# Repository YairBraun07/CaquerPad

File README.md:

# CaquerPad
4x3 macro pad with rotary encoder. Built for HackClub Blueprint Hackpad project. 

---

## 📸 Project Overview 
Here is a look at the finished and functional device.

---

## ⚡ Electronics Design

### Schematic
This is the wiring diagram showing how all components are connected.

### PCB (Printed Circuit Board)
This is the board layout design where the components are soldered.

---

## 📦Case assembly
Views of the 3D printed case and how all the parts fit together.

---

## 🛠 Bill of Materials (BOM)
List of components required to build this project.

| Component | Quantity | Details / Notes |
| :--- | :---: | :--- |
| Microcontroller | 1 | Seeed Studio XIAO RP2040 |
| Switches | 12 | e.g., Cherry MX or Gateron |
| Keycaps | 12 | *Make sure they are compatible* |
| Diodes | 12 | 1N4148 |
| Encoder | 1 | EC11 Rotary Encoder |
| LEDs | 12 | SK6812 Mini-E / WS2812B |
| Case | 1 | 3D Printed (PLA/PETG) |
| Screws | 3 | M3 x 5mm |

---

### Author
* **[Yair Braun]**

### Ethical Considerations: Google Gemini AI was utilized as a general guide throughout the entire project development, assisting with best practices, troubleshooting, and documentation structure."

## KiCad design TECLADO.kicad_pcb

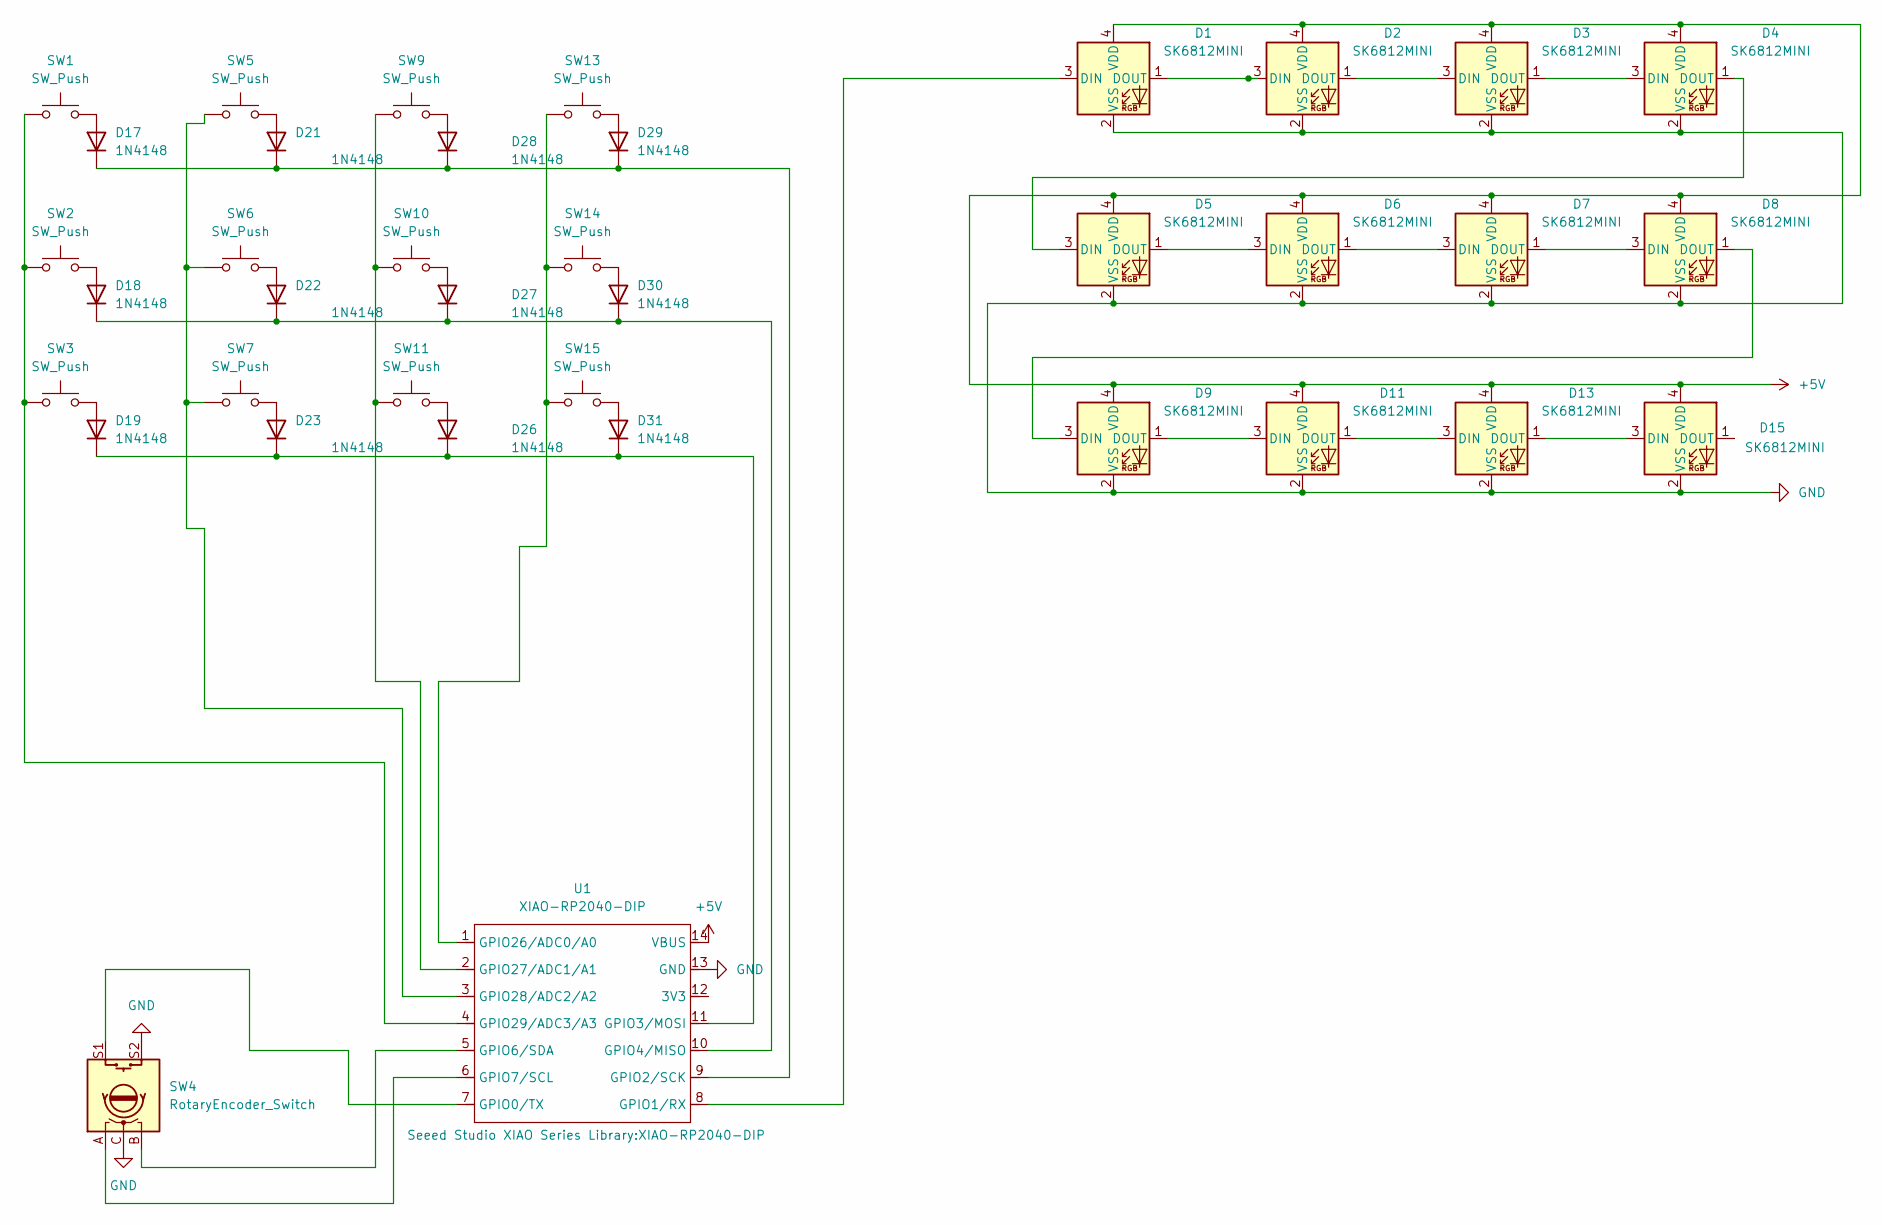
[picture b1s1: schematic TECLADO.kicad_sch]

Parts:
D1, D2, D3, D4, D5, D6, D7, D8, D9, D11, D13, D15: SK6812MINI; LED_SK6812MINI_PLCC4_3.5x3.5mm_P1.75mm
D17, D18, D19, D21, D22, D23, D26, D27, D28, D29, D30, D31: 1N4148; D_DO-35_SOD27_P7.62mm_Horizontal
SW1, SW2, SW3, SW5, SW6, SW7, SW9, SW10, SW11, SW13, SW14, SW15: SW_Push; SW_Cherry_MX_1.00u_PCB
SW4: RotaryEncoder_Switch; RotaryEncoder_Alps_EC11E-Switch_Vertical_H20mm_CircularMoun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
U1: XIAO-RP2040-DIP

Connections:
+5V: D1.4 (VDD), D2.4 (VDD), D3.4 (VDD), D4.4 (VDD), D5.4 (VDD), D6.4 (VDD), D7.4 (VDD), D8.4 (VDD), D9.4 (VDD), D11.4 (VDD), D13.4 (VDD), D15.4 (VDD), U1.14 (VBUS)
GND: D1.2 (VSS), D2.2 (VSS), D3.2 (VSS), D4.2 (VSS), D5.2 (VSS), D6.2 (VSS), D7.2 (VSS), D8.2 (VSS), D9.2 (VSS), D11.2 (VSS), D13.2 (VSS), D15.2 (VSS), SW4.C, SW4.S2, U1.13 (GND)
unnamed: D1.3 (DIN), U1.8 (GPIO1/RX)
unnamed: D1.1 (DOUT), D2.3 (DIN)
unnamed: D2.1 (DOUT), D3.3 (DIN)
unnamed: D3.1 (DOUT), D4.3 (DIN)
unnamed: D4.1 (DOUT), D5.3 (DIN)
unnamed: D5.1 (DOUT), D6.3 (DIN)
unnamed: D6.1 (DOUT), D7.3 (DIN)
unnamed: D7.1 (DOUT), D8.3 (DIN)
unnamed: D8.1 (DOUT), D9.3 (DIN)
unnamed: D9.1 (DOUT), D11.3 (DIN)
unnamed: D11.1 (DOUT), D13.3 (DIN)
unnamed: D13.1 (DOUT), D15.3 (DIN)
unnamed: D17.2 (A), SW1.2
unnamed: D17.1 (K), D21.1 (K), D28.1 (K), D29.1 (K), U1.9 (GPIO2/SCK)
unnamed: D18.2 (A), SW2.2
unnamed: D18.1 (K), D22.1 (K), D27.1 (K), D30.1 (K), U1.10 (GPIO4/MISO)
unnamed: D19.2 (A), SW3.2
unnamed: D19.1 (K), D23.1 (K), D26.1 (K), D31.1 (K), U1.11 (GPIO3/MOSI)
unnamed: D21.2 (A), SW5.2
unnamed: D22.2 (A), SW6.2
unnamed: D23.2 (A), SW7.2
unnamed: D26.2 (A), SW11.2
unnamed: D27.2 (A), SW10.2
unnamed: D28.2 (A), SW9.2
unnamed: D29.2 (A), SW13.2
unnamed: D30.2 (A), SW14.2
unnamed: D31.2 (A), SW15.2
unnamed: SW4.S1, U1.7 (GPIO0/TX)
unnamed: SW4.B, U1.5 (GPIO6/SDA)
unnamed: SW4.A, U1.6 (GPIO7/SCL)
unnamed: SW13.1, SW14.1, SW15.1, U1.1 (GPIO26/ADC0/A0)
unnamed: SW9.1, SW10.1, SW11.1, U1.2 (GPIO27/ADC1/A1)
unnamed: SW5.1, SW6.1, SW7.1, U1.3 (GPIO28/ADC2/A2)
unnamed: SW1.1, SW2.1, SW3.1, U1.4 (GPIO29/ADC3/A3)

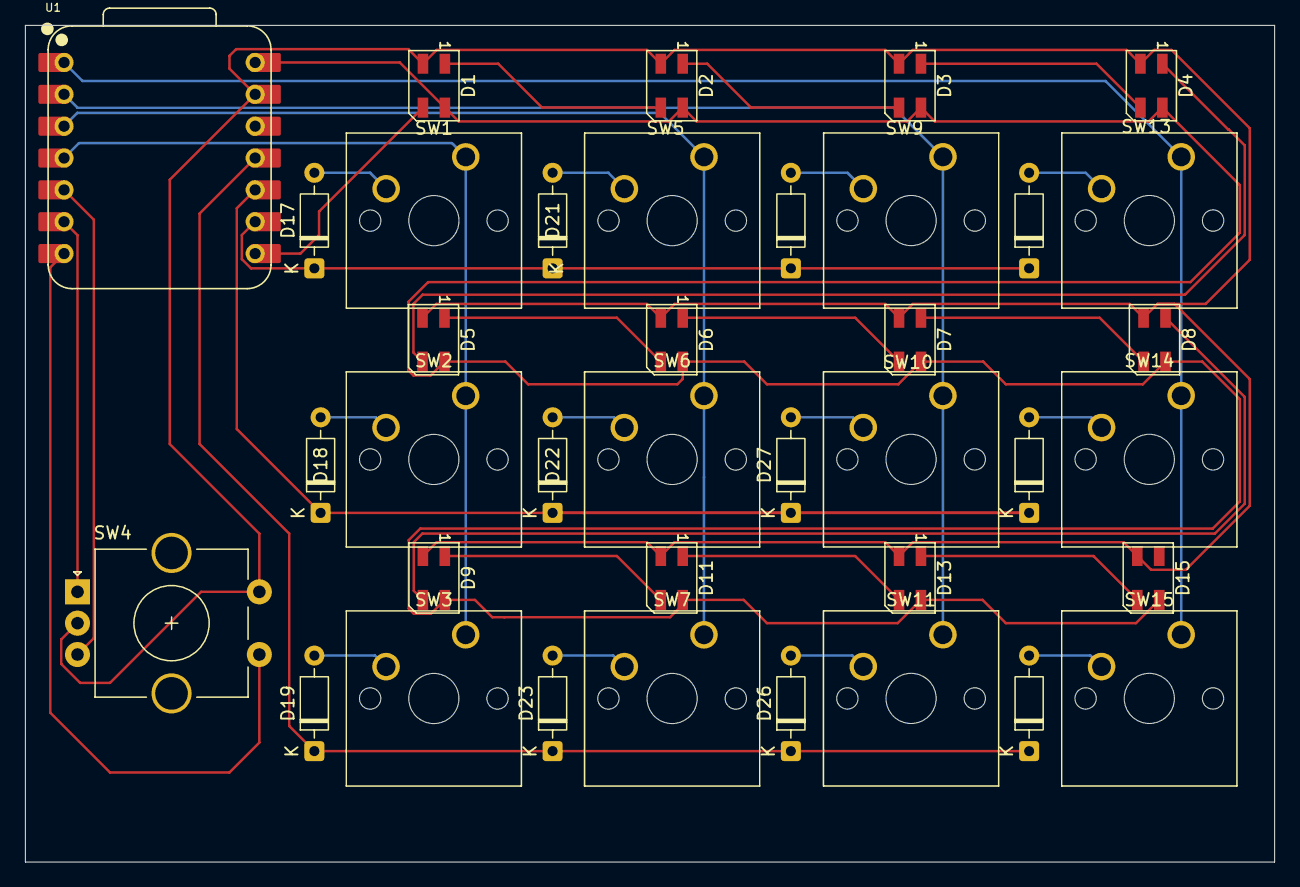
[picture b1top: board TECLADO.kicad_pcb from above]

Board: 2 copper layers, 99.6 x 66.7 mm, 38 parts (0 on the bottom side), 36 nets.

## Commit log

2025-12-14 Add files via upload
    Project file
2025-12-14 KiCad Project file
2025-12-14 Schematics File
2025-12-14 PCB Board File
2025-12-16 Case 3D Model
2025-12-16 Rename CASE_CAQUERPAD.3mf to 3D FILES/CASE_CAQUERPAD.3mf
2025-12-16 FOLDER FOR 3D MODELS
2025-12-16 CODE/FIRMWARE
2025-12-16 PHOTOS
2025-12-16 Rename PCB.png to assets/PCB.png
2025-12-16 Rename PAD_VIEW.png to assets/PAD_VIEW.png
2025-12-16 Rename SCHEMATIC.png to assets/SCHEMATIC.png
2025-12-16 Rename PAD_VIEW_2.png to assets/PAD_VIEW_2.png
2025-12-16 Rename PAD_VIEW_3.png to assets/PAD_VIEW_3.png
2025-12-16 STEP FILES
